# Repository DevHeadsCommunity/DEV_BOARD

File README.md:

# STM32 Cortex-M0 Development Board

## Project overview
Develop a low-cost development board featuring an STM32 Cortex-M0 microcontroller with integrated sensors, display, and debugging capabilities. 
The board will support USB debugging and UART communication, making it suitable for prototyping applications requiring motion sensing and environmental data collection.

## Key Features

1. Microcontroller: STM32F072C8T6 (Cortex-M0, USB Full-Speed 2.0)

2. Sensors:

i. LSM6DS3 (6-axis IMU: Gyroscope + Accelerometer)

ii. QMC5883L (Magnetometer)

iii. Temperature sensor

3. Display Options:

i. 1x 7-segment display or 4x LEDs (whichever is cheaper)

4. Onboard Debugging:

i. USB-to-UART via CH340T

5. Supports automatic bootloader mode via DTR/RTS

6. Expansion & Connectivity:

i. Multiple GPIOs for prototyping

ii. Space for additional headers

## Design and Development

The hardware design is being developed using KiCad, focusing on creating a compact and cost-effective PCB layout. 
This project does not include firmware development but provides a solid hardware platform for future software implementation.

## Components needed
1. STM32F072C8T6 Microcontroller: Core processing unit

2. LSM6DS3 + QMC5883L: Motion sensing and magnetometer

3. 7-segment display / LEDs: Visual output

4. CH340T USB-to-UART: Serial communication and flashing support

5. Supporting Components: Resistors, capacitors, headers, etc.

##   PCB Design Plan

1. Schematic Design

i. Connect STM32F072C8T6 with sensors, display, and USB debugging interface.

ii. Ensure power regulation and signal integrity.

2. PCB Layout

i. Optimize component placement for a compact and efficient design.

ii. Route signals carefully to minimize interference.

3. Prototype & Testing

i. Manufacture PCB and verify electrical connections.

ii. Validate power delivery and communication between components.

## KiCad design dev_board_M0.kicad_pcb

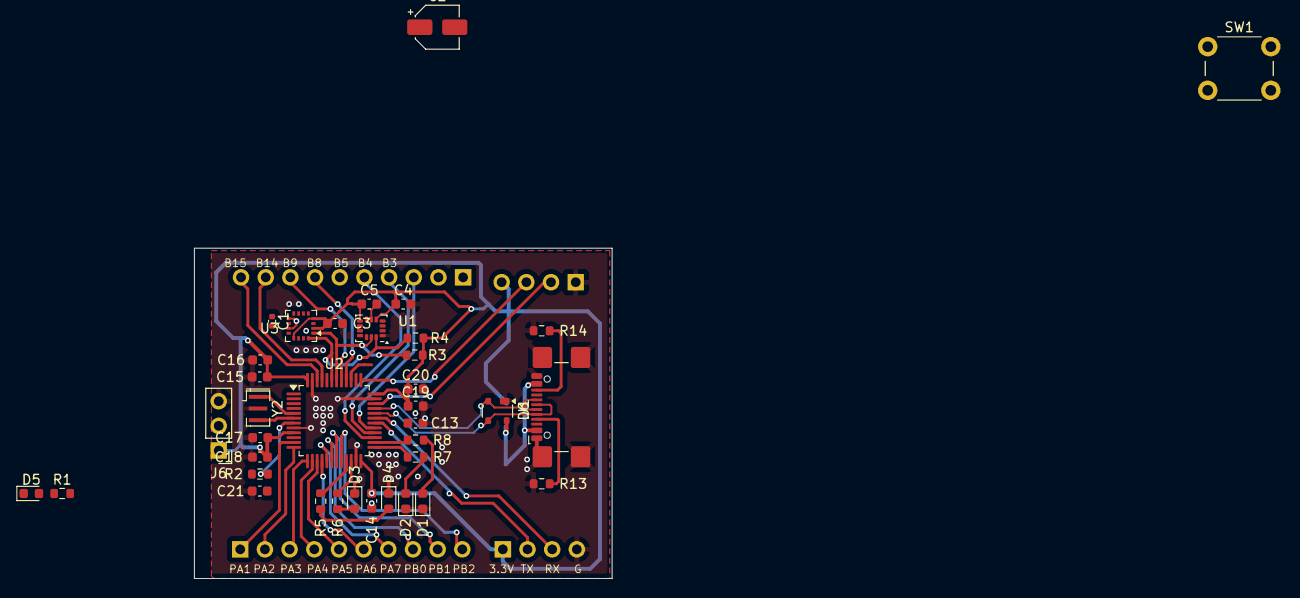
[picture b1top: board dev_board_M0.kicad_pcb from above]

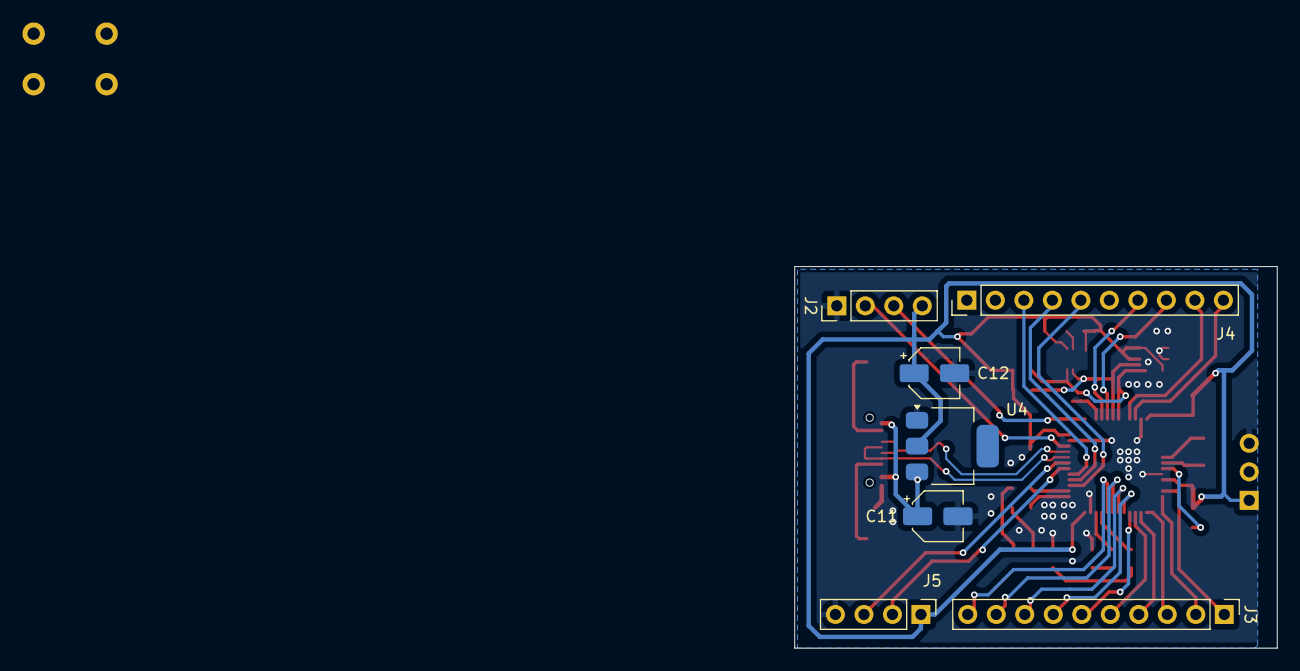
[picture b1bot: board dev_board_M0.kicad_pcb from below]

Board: 2 copper layers, 43.0 x 34.0 mm, 44 parts (7 on the bottom side), 47 nets.

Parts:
C1: 0.22uF; C_0402_1005Metric
C2: 4.7uF; CP_Elec_4x4.5
C3, C4, C5, C13, C14, C15, C19: 0.1uf; C_0603_1608Metric
C11: 10uF,50v; CP_Elec_4x5.4
C12: 22uF,50v; CP_Elec_4x5.4
C16, C20: 4.7uf; C_0603_1608Metric
C17: 10nf; C_0603_1608Metric
C18, C21: 1uf; C_0603_1608Metric
D1, D2, D3, D4: LED; LED_0603_1608Metric
D5: RED; LED_0603_1608Metric
D6: PRTR5V0U2X; SOT-143
J1: USB_C_Receptacle_USB2.0_16P; USB_C_Receptacle_GCT_USB4110
J2: DEBUGGER; PinHeader_1x04_P2.54mm_Vertical
J3: PIN_HEADER1; PinHeader_1x10_P2.54mm_Vertical
J4: PIN_HEADER2; PinHeader_1x10_P2.54mm_Vertical
J5: USART1; PinHeader_1x04_P2.54mm_Vertical
J6: DFU; PinHeader_1x03_P2.54mm_Vertical
R1, R2, R5, R6, R7, R8: 5k1; R_0603_1608Metric
R3, R4: 10K; R_0603_1608Metric
R13, R14: 5.1k; R_0603_1608Metric
SW1: SW_MEC_5E; SW_PUSH_6mm
U1: LSM6DS3; LGA-14_3x2.5mm_P0.5mm_LayoutBorder3x4y
U2: STM32F072C8Tx; LQFP-48_7x7mm_P0.5mm
U3: HMC5883L; LGA-16_3x3mm_P0.5mm
U4: TLV1117-33IDCYR; SOT-223
Y2: 8MhZ; Resonator_SMD_Murata_CSTxExxV-3Pin_3.0x1.1mm

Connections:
+3.3V: C3.1, C4.1, C5.1, C12.1, C13.1, C14.1, C15.1, C16.1, C17.1, C18.1, C19.1, C20.1, J2.4, J5.1, J6.1, R1.2, R2.2, R3.2, R4.2, U1.5 (VDDIO), U1.8 (VDD), U2.9 (VDDA), U2.24 (VDD), U2.36 (VDDIO2), U2.48 (VDD), U3.2 (VDD), U3.4 (S1), U3.13 (VDDIO), U4.2 (VO)
+5V: C11.1, D6.4 (VCC), J1.A4 (VBUS), J1.A9 (VBUS), J1.B4 (VBUS), J1.B9 (VBUS), U4.3 (VI)
/NRST: C21.1, R2.1, SW1.1, U2.7 (NRST)
/PA1: J3.1, U2.11 (PA1)
/PA2: J3.2, U2.12 (PA2)
/PA3: J3.3, U2.13 (PA3)
/PA4: J3.4, U2.14 (PA4)
/PA5: J3.5, U2.15 (PA5)
/PA6: J3.6, U2.16 (PA6)
/PA7: J3.7, U2.17 (PA7)
/PA8: J4.3, U2.29 (PA8)
/PA11: D6.3 (I/O2), J1.A7 (D-), J1.B7 (D-), U2.32 (PA11)
/PA12: D6.2 (I/O1), J1.A6 (D+), J1.B6 (D+), U2.33 (PA12)
/PB0: J3.8, U2.18 (PB0)
/PB1: J3.9, U2.19 (PB1)
/PB2: J3.10, U2.20 (PB2)
/PB3: J4.6, U2.39 (PB3)
/PB4: J4.7, U2.40 (PB4)
/PB5: J4.8, U2.41 (PB5)
/PB8: J4.9, U2.45 (PB8)
/PB9: J4.10, U2.46 (PB9)
/PB14: J4.5, U2.27 (PB14)
/PB15: J4.4, U2.28 (PB15)
/SCL: R3.1, U1.13 (SCL), U2.42 (PB6), U3.1 (SCL)
/SDA: R4.1, U1.14 (SDA), U2.43 (PB7), U3.16 (SDA)
/SWDIO: J2.2, U2.34 (PA13)
/SWLCK: J2.3, U2.37 (PA14)
/USART1_RX: J5.3, U2.31 (PA10)
/USART1_TX: J5.2, U2.30 (PA9)
GND: C2.2, C3.2, C4.2, C5.2, C11.2, C12.2, C13.2, C14.2, C15.2, C16.2, C17.2, C18.2, C19.2, C20.2, C21.2, D1.1 (K), D2.1 (K), D3.1 (K), D4.1 (K), D5.1 (K), D6.1 (GND), J1.A1 (GND), J1.A12 (GND), J1.B1 (GND), J1.B12 (GND), J1.S1 (SHIELD), J2.1, J5.4, J6.3, R13.1, R14.1, SW1.2, U1.1 (SDO/SA0), U1.2 (SDX), U1.6 (GND), U1.7 (GND), U2.8 (VSSA), U2.23 (VSS), U2.35 (VSS), U2.47 (VSS), U3.9 (GND@1), U3.11 (GND@2), U4.1 (GND), Y2.2
unnamed: D1.2 (A), R8.2
unnamed: D2.2 (A), R7.2
unnamed: D3.2 (A), R6.2
unnamed: D4.2 (A), R5.2
unnamed: D5.2 (A), R1.1
unnamed: J1.A5 (CC1), R13.2
unnamed: J1.B5 (CC2), R14.2
unnamed: J6.2, U2.44 (BOOT0)
unnamed: R5.1, U2.21 (PB10)
unnamed: R6.1, U2.22 (PB11)
unnamed: R7.1, U2.25 (PB12)
unnamed: R8.1, U2.26 (PB13)
unnamed: U2.5 (PF0), Y2.1
unnamed: U2.6 (PF1), Y2.3
unnamed: C2.1, U3.10 (C1)
unnamed: C1.2, U3.12 (SETC)
unnamed: C1.1, U3.8 (SETP)

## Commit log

2025-02-17 created the design file
2025-02-17 Create README.md
    Description of project
2025-02-18 Wired gyro/accel and magnetometer
2025-02-20 Finished up the schematic
